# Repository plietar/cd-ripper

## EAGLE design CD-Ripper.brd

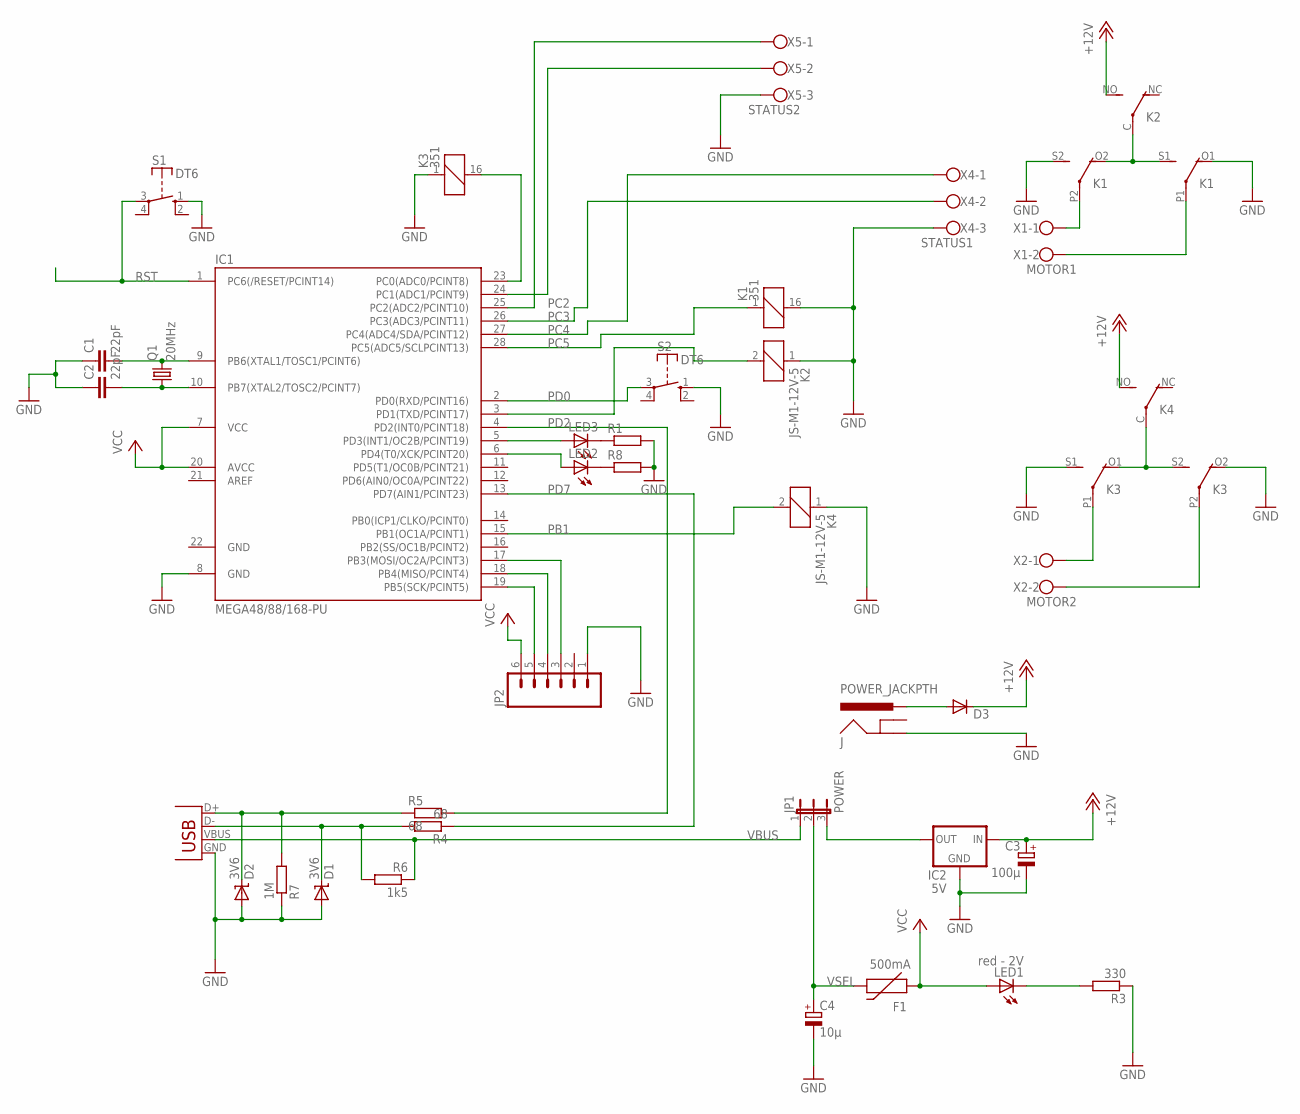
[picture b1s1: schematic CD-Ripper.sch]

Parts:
C1, C2: 22pF; C2.5-3
C3: 100µ; E2,5-6E
C4: 10µ; E2,5-7
D1, D2: 3V6; DIODE-ZENER
D3: 1N4148DO35-10; DO35-10
F1: 500mA; PTC
IC1: MEGA48/88/168-PU; DIL28-3
IC2: 5V; 78XXL
J: POWER_JACKPTH; POWER_JACK_PTH
JP1: POWER; JP2
JP2: M06SIP; 1X06
K1, K3: 351
K2, K4: JS-M1-12V-5; JS-M
LED1: red - 2V; LED5MM
LED2, LED3: LED5MM
Q1: 20MHz; HC49/S
R1, R8: R-EU_0204/7; 0204/7
R3: 330; 0204/7
R4, R5: 68; 0204/7
R6: 1k5; 0204/7
R7: 1M; 0204/7
S1, S2: DT6
X1: MOTOR1; W237-102
X2: MOTOR2; W237-102
X3: USBPTH; USB-B-PTH
X4: STATUS1; W237-103
X5: STATUS2; W237-103

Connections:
+12V: C3.+, D3.C, IC2.IN, K2.NO (S), K4.NO (S)
D+: D2.P$1 (C), R5.1, R7.2, X3.D+
D-: D1.P$1 (C), R4.2, R6.2, X3.D-
GND: C1.1, C2.1, C3.-, C4.-, D1.P$2 (A), D2.P$2 (A), IC1.8 (GND), IC1.22 (GND), IC2.GND, J.GND, JP2.1, K1.16 (2), K1.O1 (O), K1.S2 (S), K2.1, K3.1, K3.O2 (O), K3.S1 (S), K4.1, R1.2, R3.1, R7.1, R8.2, S1.1 (S), S2.1 (S), X3.GND, X4.3, X5.3
unnamed: LED1.K (C), R3.2
unnamed: D3.A, J.PWR
unnamed: K1.P2, X1.1
unnamed: K1.P1, X1.2
unnamed: K3.P1, X2.1
unnamed: K3.P2, X2.2
unnamed: IC1.5 (PD3(INT1/OC2B/PCINT19)), LED3.A
unnamed: IC1.6 (PD4(T0/XCK/PCINT20)), LED2.A
unnamed: LED3.K (C), R1.1
unnamed: IC1.25 (PC2(ADC2/PCINT10)), X5.1
unnamed: IC1.24 (PC1(ADC1/PCINT9)), X5.2
unnamed: K1.O2 (O), K1.S1 (S), K2.C
unnamed: K3.O1 (O), K3.S2 (S), K4.C
unnamed: LED2.K (C), R8.1
unnamed: IC1.19 (PB5(SCK/PCINT5)), JP2.5
unnamed: IC1.18 (PB4(MISO/PCINT4)), JP2.4
unnamed: IC1.17 (PB3(MOSI/OC2A/PCINT3)), JP2.3
PB1: IC1.15 (PB1(OC1A/PCINT1)), K4.2
PB2: IC1.23 (PC0(ADC0/PCINT8)), K3.16 (2)
PC2: IC1.26 (PC3(ADC3/PCINT11)), X4.2
PC3: IC1.27 (PC4(ADC4/SDA/PCINT12)), X4.1
PC4: IC1.28 (PC5(ADC5/SCLPCINT13)), K1.1
PC5: IC1.3 (PD1(TXD/PCINT17)), K2.2
PD0: IC1.2 (PD0(RXD/PCINT16)), S2.3
PD2: IC1.4 (PD2(INT0/PCINT18)), R5.2
PD7: IC1.13 (PD7(AIN1/PCINT23)), R4.1
RST: IC1.1 (PC6(/RESET/PCINT14)), S1.3
VBUS: JP1.1, R6.1, X3.VBUS
VCC: F1.P$1 (1), IC1.7 (VCC), IC1.20 (AVCC), JP2.6, LED1.A
VREG: IC2.OUT, JP1.3
VSEL: C4.+, F1.P$2 (2), JP1.2
XTAL1: C1.2, IC1.9 (PB6(XTAL1/TOSC1/PCINT6)), Q1.2
XTAL2: C2.2, IC1.10 (PB7(XTAL2/TOSC2/PCINT7)), Q1.1

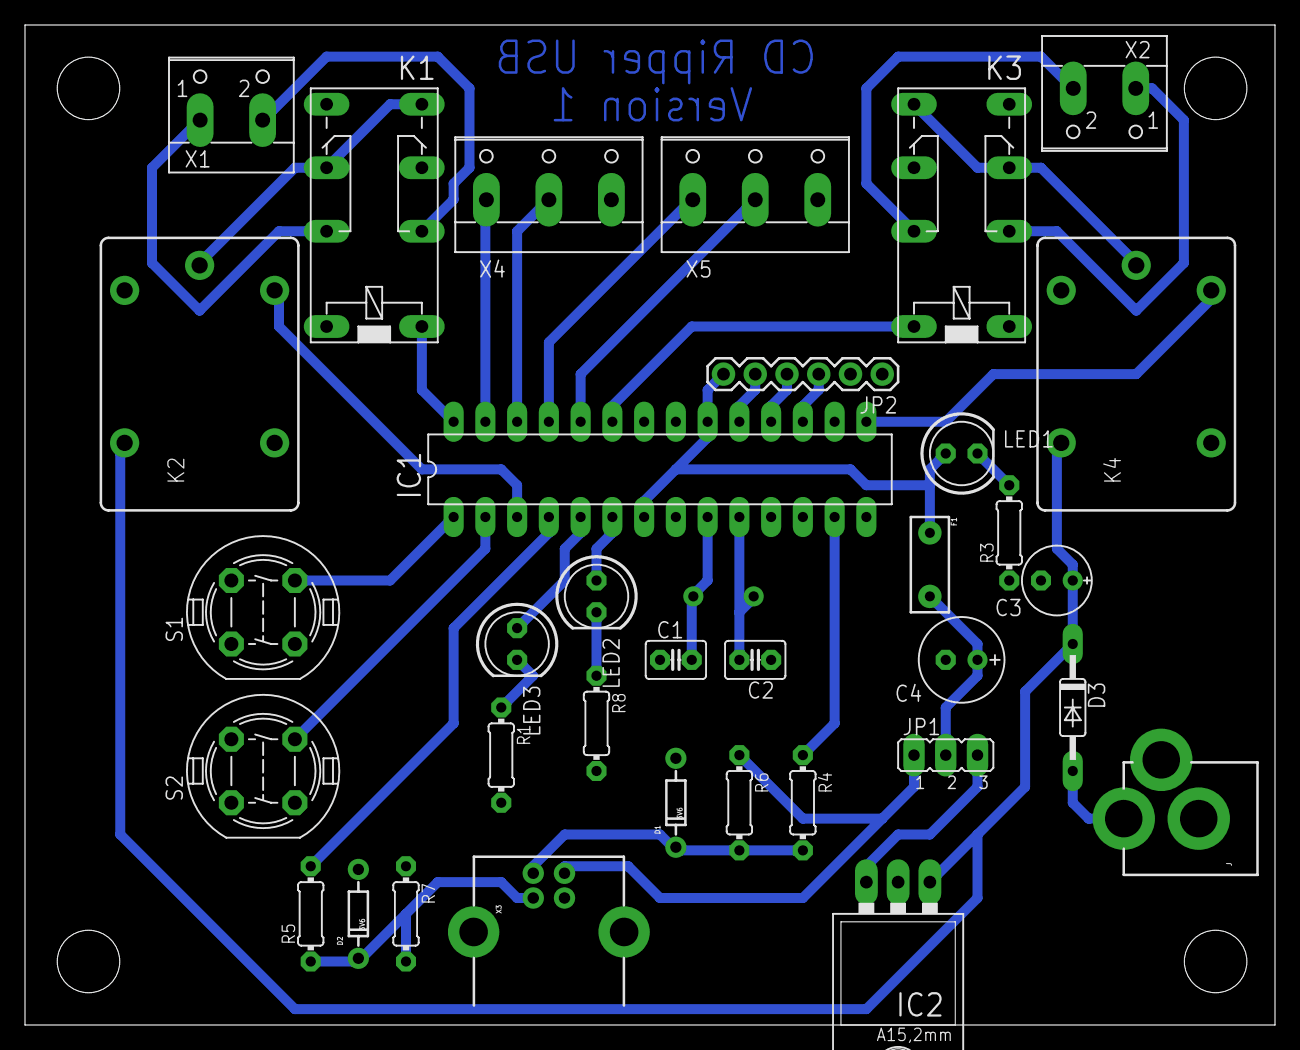
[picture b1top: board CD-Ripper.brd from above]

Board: 2 copper layers, 100.0 x 80.0 mm, 35 parts (1 on the bottom side), 37 nets.

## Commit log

2012-05-20 Initial commit.
2012-05-20 Added the files.
2012-05-23 Changed ICSP header.
2012-05-23 Removed the autorouter statistics file.
